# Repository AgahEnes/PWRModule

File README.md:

# PWRModule
In this article we introduce our power distribution modules. These boards help to get rid of long and heavy power cables. Circuit boards are reliable for connection instead of cables. Some of them distribute power to parallel or serial ways and others regulates high voltage power to desired values.
 PCB's have XT60 connector inputs for battery and XT60 outputs to power sensors or other kind of stuffs on our UAVs. Every output connection getting power from Li-Po battery and regulate this for desired value. By using resistors we adjust the out voltage. Both of the boards for our UAVs and for regulate power.
 One of them designed for unmanned ground vehicle (UGV) and is capable of meeting the power requirements of the onboard sensors and autopilot. There is also a motor drive system that will enable the UAG to move.
For orders https://jlcpcb.com/RAT is reliable.

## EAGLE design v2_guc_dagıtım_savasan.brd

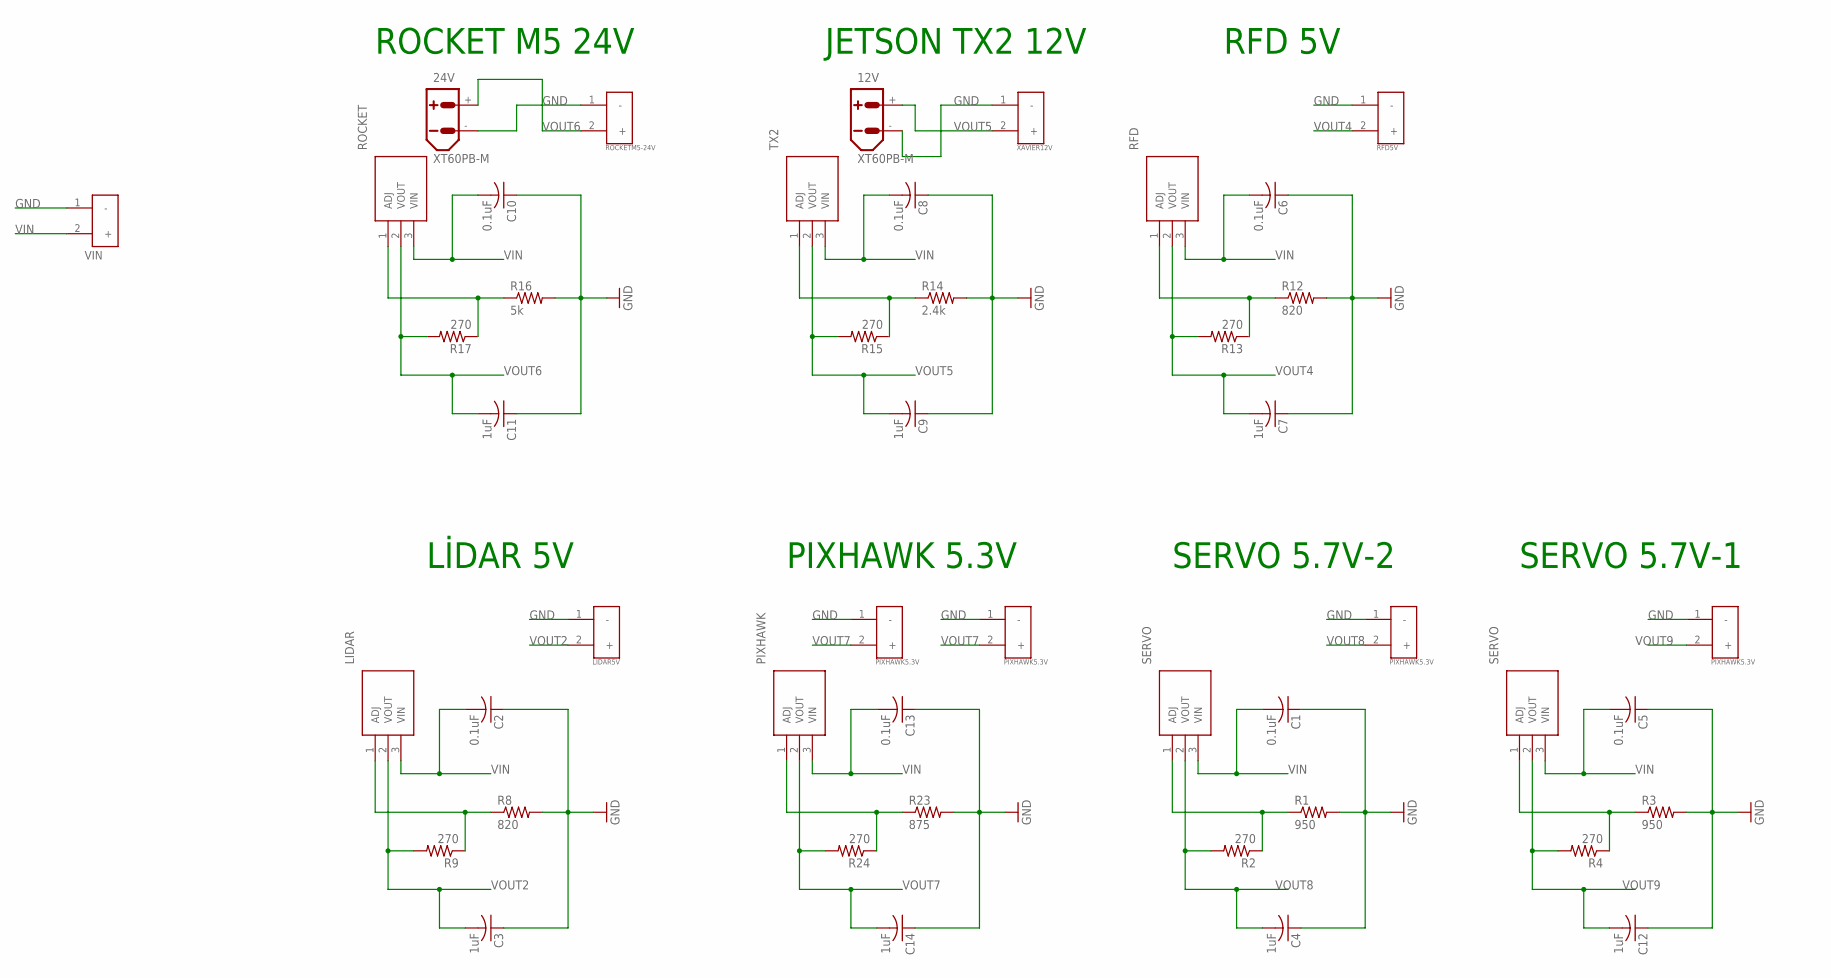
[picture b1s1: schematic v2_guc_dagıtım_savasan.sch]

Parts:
12V, 24V: XT60PB-M
C1, C2, C5, C6, C8, C10, C13: 0.1uF; C0402K
C3, C4, C7, C9, C11, C12, C14: 1uF; C0402K
IC5: LIDAR; TO254P470X1028X1955-3P
IC7: RFD; TO254P470X1028X1955-3P
IC8: TX2; TO254P470X1028X1955-3P
IC9: ROCKET; TO254P470X1028X1955-3P
IC13: PIXHAWK; TO254P470X1028X1955-3P
J3: VIN; AMASS_XT60-M
LIDAR5V: LIDAR5V; AMASS_XT60-M
PIXHAWK5.3V-1, PIXHAWK5.3V-2: PIXHAWK5.3V; AMASS_XT60-M
R1, R3: 950; R0805
R2, R4, R9, R13, R15, R17, R24: 270; R0805
R8, R12: 820; R0805
R14: 2.4k; R0805
R16: 5k; R0805
R23: 875; R0805
RFD5V: RFD5V; AMASS_XT60-M
ROCKETM5-24V: ROCKETM5-24V; AMASS_XT60-M
SERVO5.7V-1, SERVO5.7V-2: PIXHAWK5.3V; AMASS_XT60-M
SERVO-1, SERVO-2: SERVO; TO254P470X1028X1955-3P
TX2-12V: XAVIER12V; AMASS_XT60-M

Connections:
GND: 12V.-, 24V.-, C1.1, C2.1, C3.1, C4.1, C5.1, C6.1, C7.1, C8.1, C9.1, C10.1, C11.1, C12.1, C13.1, C14.1, J3.1 (-), LIDAR5V.1 (-), PIXHAWK5.3V-1.1 (-), PIXHAWK5.3V-2.1 (-), R1.2, R3.2, R8.2, R12.2, R14.2, R16.2, R23.2, RFD5V.1 (-), ROCKETM5-24V.1 (-), SERVO5.7V-1.1 (-), SERVO5.7V-2.1 (-), TX2-12V.1 (-)
unnamed: R1.1, R2.1, SERVO-2.1 (ADJ)
unnamed: R3.1, R4.1, SERVO-1.1 (ADJ)
unnamed: IC7.1 (ADJ), R12.1, R13.1
unnamed: IC5.1 (ADJ), R8.1, R9.1
unnamed: IC8.1 (ADJ), R14.1, R15.1
unnamed: IC9.1 (ADJ), R16.1, R17.1
unnamed: IC13.1 (ADJ), R23.1, R24.1
VIN: C1.2, C2.2, C5.2, C6.2, C8.2, C10.2, C13.2, IC5.3 (VIN), IC7.3 (VIN), IC8.3 (VIN), IC9.3 (VIN), IC13.3 (VIN), J3.2 (+), SERVO-1.3 (VIN), SERVO-2.3 (VIN)
VOUT2: C3.2, IC5.2 (VOUT), LIDAR5V.2 (+), R9.2
VOUT4: C7.2, IC7.2 (VOUT), R13.2, RFD5V.2 (+)
VOUT5: 12V.+, C9.2, IC8.2 (VOUT), R15.2, TX2-12V.2 (+)
VOUT6: 24V.+, C11.2, IC9.2 (VOUT), R17.2, ROCKETM5-24V.2 (+)
VOUT7: C14.2, IC13.2 (VOUT), PIXHAWK5.3V-1.2 (+), PIXHAWK5.3V-2.2 (+), R24.2
VOUT8: C4.2, R2.2, SERVO5.7V-2.2 (+), SERVO-2.2 (VOUT)
VOUT9: C12.2, R4.2, SERVO5.7V-1.2 (+), SERVO-1.2 (VOUT)

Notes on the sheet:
ROCKET M5 24V
JETSON TX2 12V
RFD 5V
LİDAR 5V
PIXHAWK 5.3V
SERVO 5.7V-2
SERVO 5.7V-1

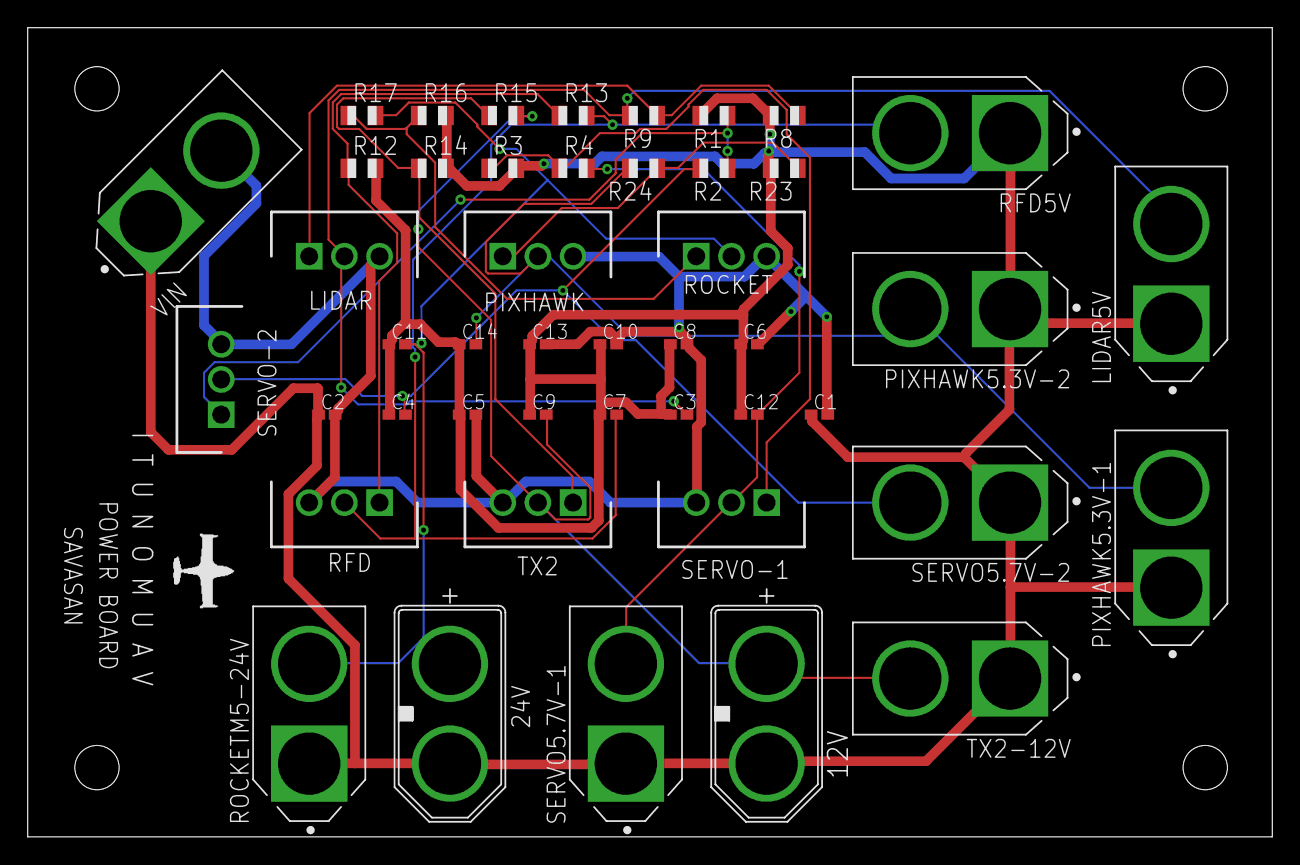
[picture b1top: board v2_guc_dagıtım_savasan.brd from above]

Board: 2 copper layers, 89.8 x 58.4 mm, 46 parts (0 on the bottom side), 16 nets.

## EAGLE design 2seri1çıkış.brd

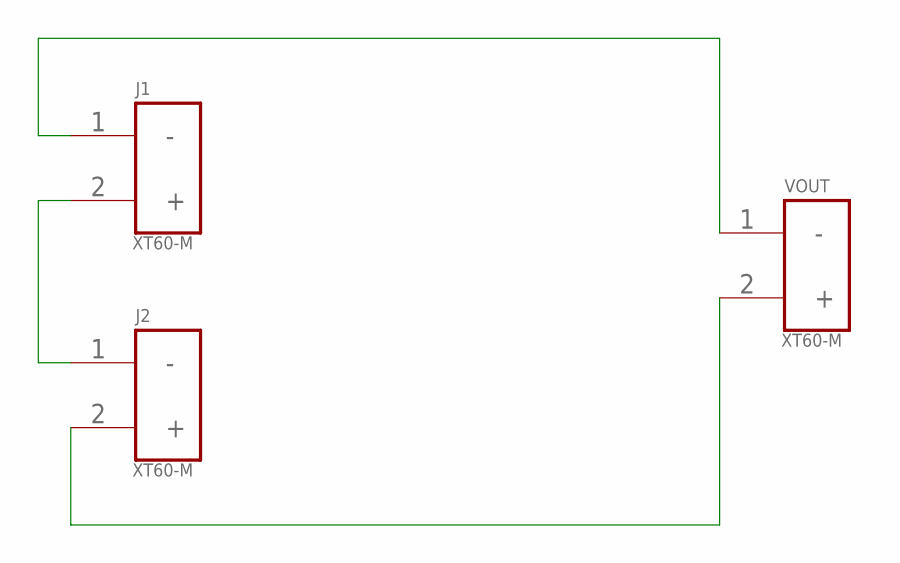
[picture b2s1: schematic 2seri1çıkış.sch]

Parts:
J1, J2: XT60-M; AMASS_XT60-M
VOUT: XT60-M; AMASS_XT60-M

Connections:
unnamed: J1.2 (+), J2.1 (-)
unnamed: J2.2 (+), VOUT.2 (+)
unnamed: J1.1 (-), VOUT.1 (-)

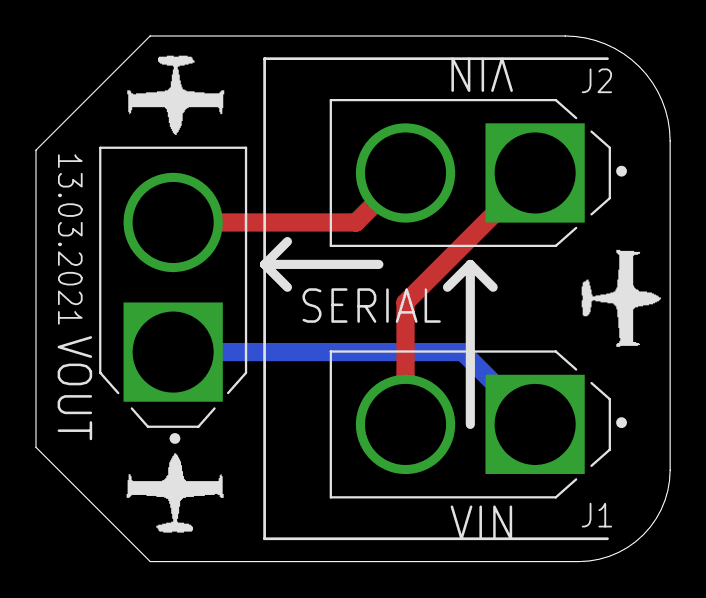
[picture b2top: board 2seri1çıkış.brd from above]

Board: 2 copper layers, 35.2 x 29.2 mm, 3 parts (0 on the bottom side), 3 nets.

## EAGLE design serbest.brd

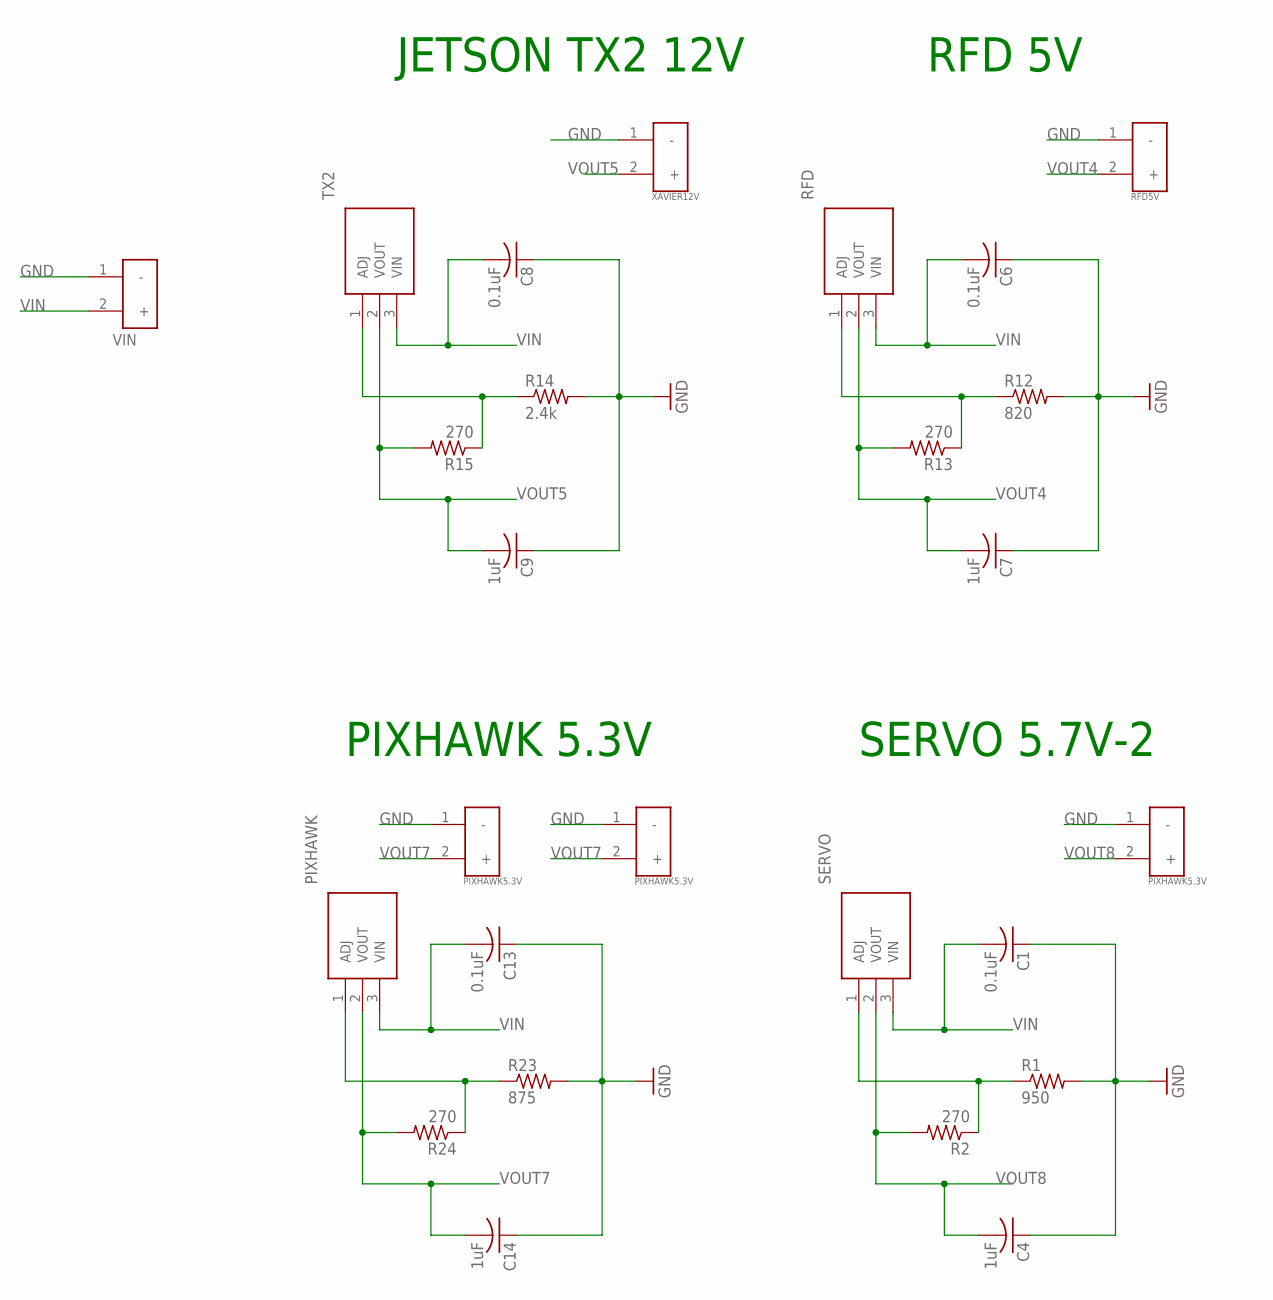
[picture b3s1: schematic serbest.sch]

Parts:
C1, C6, C8, C13: 0.1uF; C0402K
C4, C7, C9, C14: 1uF; C0402K
J3: VIN; AMASS_XT60-M
PIXHAWK: PIXHAWK; TO254P470X1028X1955-3P
PIXHAWK5.3V-1, PIXHAWK5.3V-2: PIXHAWK5.3V; AMASS_XT60-M
R1: 950; R0805
R2, R13, R15, R24: 270; R0805
R12: 820; R0805
R14: 2.4k; R0805
R23: 875; R0805
RFD: RFD; TO254P470X1028X1955-3P
RFD5V: RFD5V; AMASS_XT60-M
SERVO5.7V-2: PIXHAWK5.3V; AMASS_XT60-M
SERVO-2: SERVO; TO254P470X1028X1955-3P
TX2: TX2; TO254P470X1028X1955-3P
TX2-12V: XAVIER12V; AMASS_XT60-M

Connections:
GND: C1.1, C4.1, C6.1, C7.1, C8.1, C9.1, C13.1, C14.1, J3.1 (-), PIXHAWK5.3V-1.1 (-), PIXHAWK5.3V-2.1 (-), R1.2, R12.2, R14.2, R23.2, RFD5V.1 (-), SERVO5.7V-2.1 (-), TX2-12V.1 (-)
unnamed: R1.1, R2.1, SERVO-2.1 (ADJ)
unnamed: R12.1, R13.1, RFD.1 (ADJ)
unnamed: R14.1, R15.1, TX2.1 (ADJ)
unnamed: PIXHAWK.1 (ADJ), R23.1, R24.1
VIN: C1.2, C6.2, C8.2, C13.2, J3.2 (+), PIXHAWK.3 (VIN), RFD.3 (VIN), SERVO-2.3 (VIN), TX2.3 (VIN)
VOUT4: C7.2, R13.2, RFD.2 (VOUT), RFD5V.2 (+)
VOUT5: C9.2, R15.2, TX2.2 (VOUT), TX2-12V.2 (+)
VOUT7: C14.2, PIXHAWK.2 (VOUT), PIXHAWK5.3V-1.2 (+), PIXHAWK5.3V-2.2 (+), R24.2
VOUT8: C4.2, R2.2, SERVO5.7V-2.2 (+), SERVO-2.2 (VOUT)

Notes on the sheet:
JETSON TX2 12V
RFD 5V
PIXHAWK 5.3V
SERVO 5.7V-2

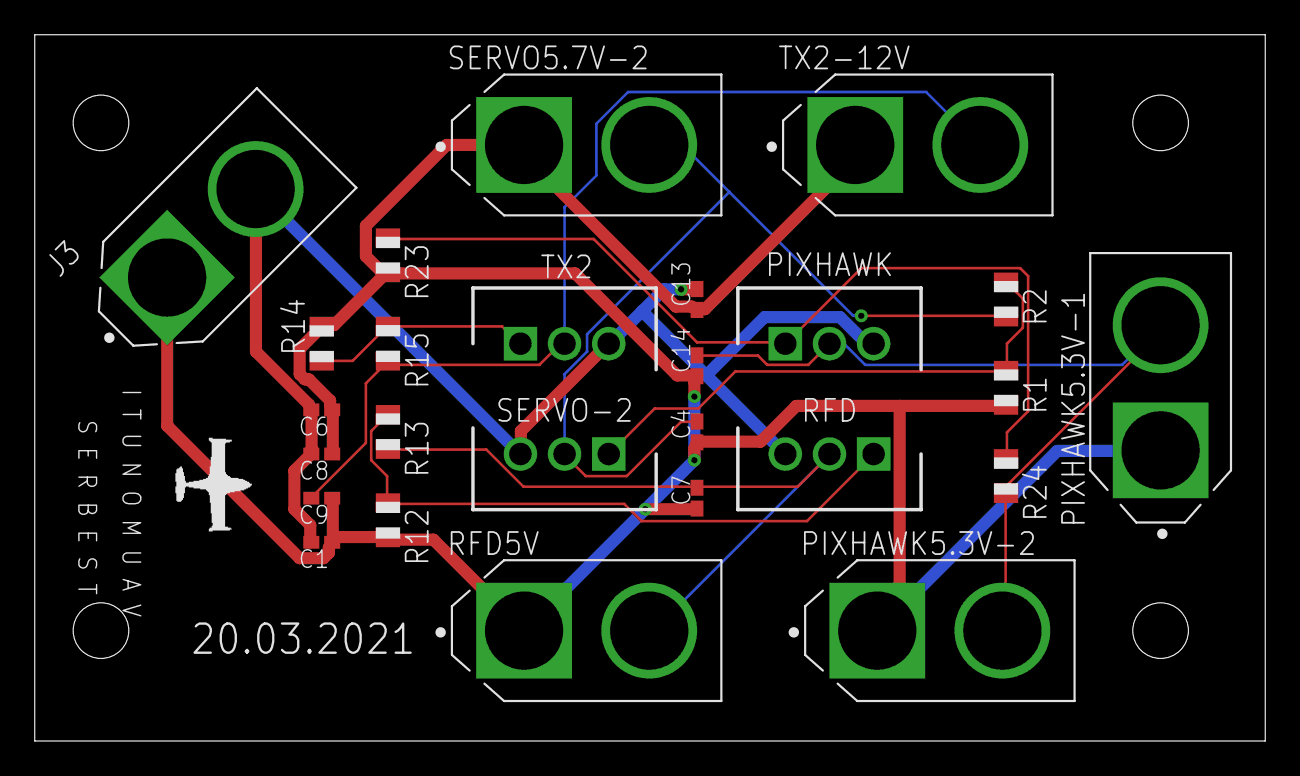
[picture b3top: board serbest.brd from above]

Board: 2 copper layers, 70.8 x 40.6 mm, 26 parts (0 on the bottom side), 10 nets.

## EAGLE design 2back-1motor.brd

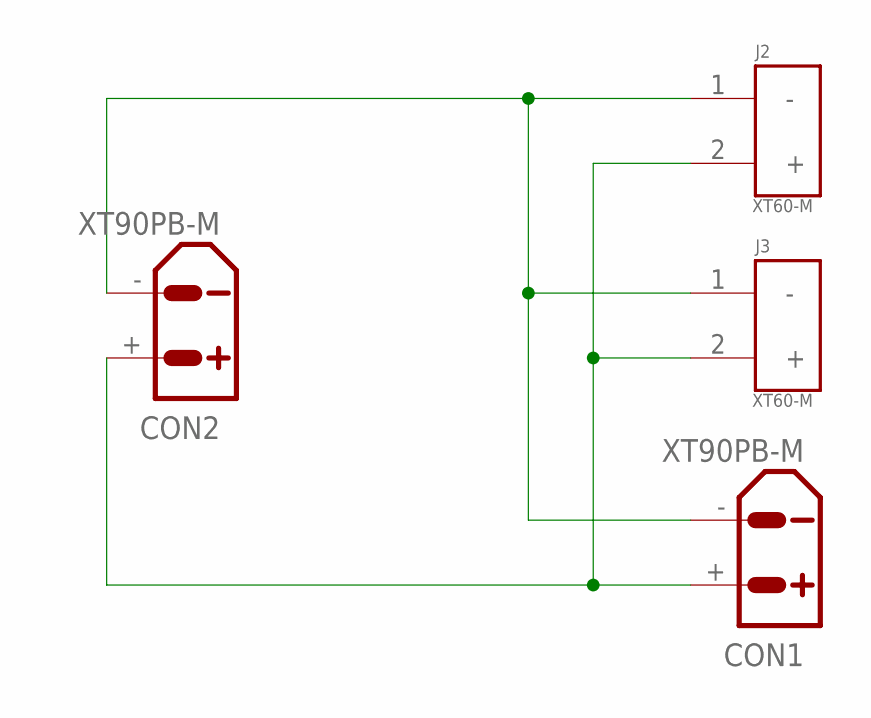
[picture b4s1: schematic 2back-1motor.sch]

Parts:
CON1, CON2: XT90PB-M
J2, J3: XT60-M; AMASS_XT60-M

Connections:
unnamed: CON1.-, CON2.-, J2.1 (-), J3.1 (-)
unnamed: CON1.+, CON2.+, J2.2 (+), J3.2 (+)

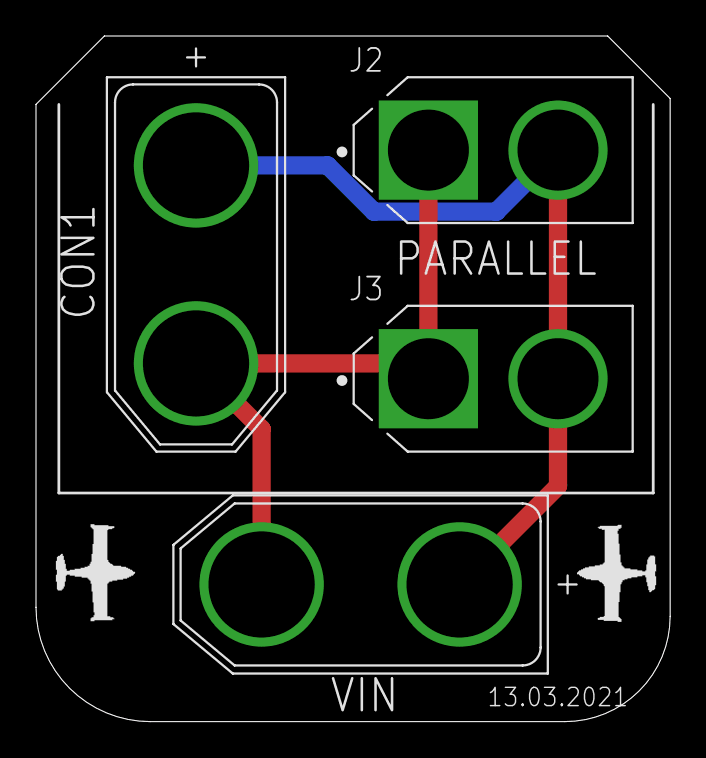
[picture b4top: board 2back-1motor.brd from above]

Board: 2 copper layers, 35.2 x 38.1 mm, 4 parts (0 on the bottom side), 2 nets.

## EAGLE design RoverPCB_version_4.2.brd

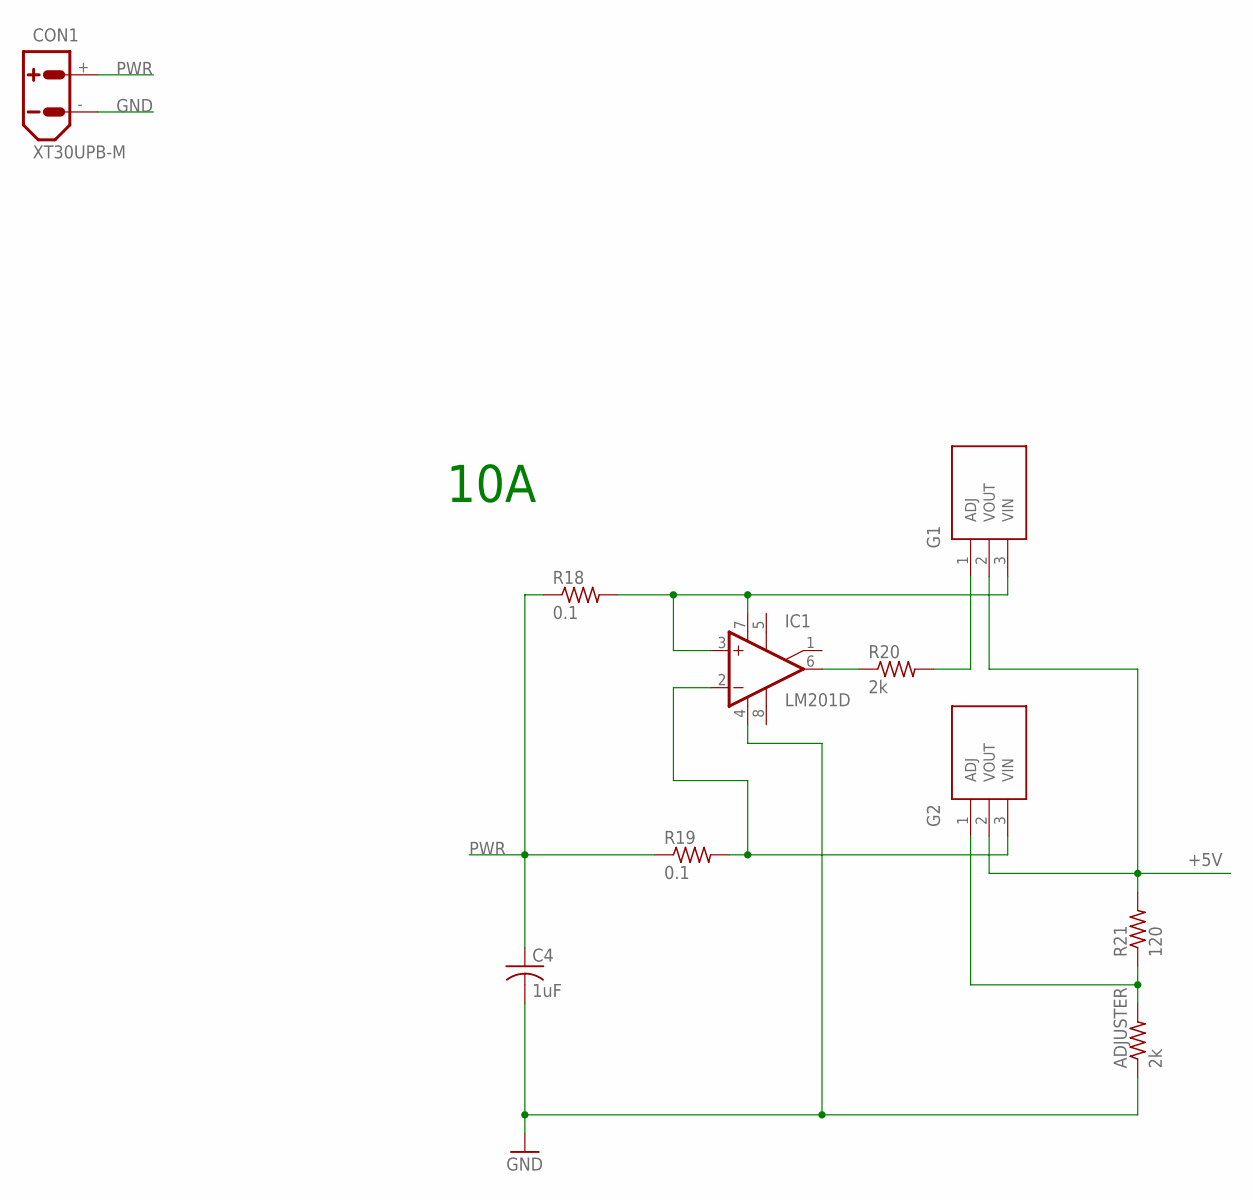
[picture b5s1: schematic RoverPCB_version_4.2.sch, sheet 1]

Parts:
ADJUSTER: 2k; 0204/5
C4: 1uF; C0402K
CON1: XT30UPB-M
IC1: LM201D; SO08
IC11: G1; TO254P470X1028X1955-3P
IC12: G2; TO254P470X1028X1955-3P
R18, R19: 0.1; M1206
R20: 2k; R0805
R21: 120; R0805

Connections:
+5V: IC11.2 (VOUT), IC12.2 (VOUT), R21.2; also elsewhere on the board
GND: ADJUSTER.1, C4.2, CON1.-, IC1.4 (V-); also elsewhere on the board
unnamed: IC11.1 (ADJ), R20.2
unnamed: IC1.6 (OUT), R20.1
unnamed: ADJUSTER.2, IC12.1 (ADJ), R21.1
unnamed: IC1.3 (+IN), IC1.7 (V+), IC11.3 (VIN), R18.2
unnamed: IC1.2 (-IN), IC12.3 (VIN), R19.2
PWR: C4.1, CON1.+, R18.1, R19.1; also elsewhere on the board

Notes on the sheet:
10A

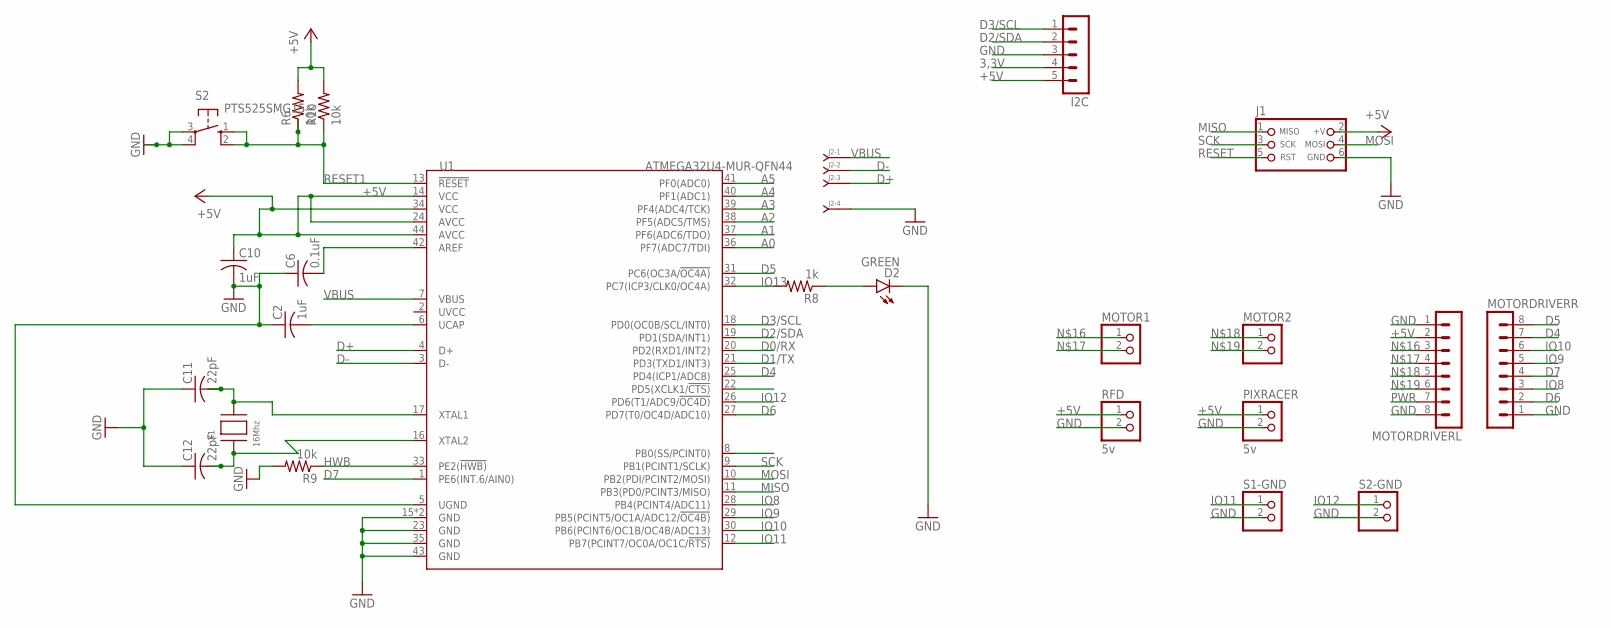
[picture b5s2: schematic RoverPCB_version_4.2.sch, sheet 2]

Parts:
C2, C10: 1uF; C0805
C6: 0.1uF; C0805
C11, C12: 22pF; C0805
D2: GREEN; LED-0603
I2C: MA05-1
J1: CON_HEADER_PRG_AVR_ICSP-PTH; HEADER_PRG_2X03
J2: J-04-SIP-100; SIP-100-04
MOTOR1, MOTOR2: PINHD-1X2; 1X02
MOTORDRIVERL: MA08-1
MOTORDRIVERR: MA08-1
PIXRACER: 5v; 1X02
R6, R9, R10: 10k; R0805
R8: 1k; R0805
RFD: 5v; 1X02
S1-GND, S2-GND: PINHD-1X2; 1X02
S2: PTS525SMG15; SMG15
U1: ATMEGA32U4-MUR-QFN44; QFN44G-0.5-7X7MM
X1: 16Mhz; NX5032

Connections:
3,3V: I2C.4
+5V: C10.1, I2C.5, J1.2 (+V), MOTORDRIVERL.2, PIXRACER.1, R6.2, R10.2, RFD.1, U1.14 (VCC), U1.24 (AVCC), U1.34 (VCC), U1.44 (AVCC); also elsewhere on the board
A0: U1.36 (PF7(ADC7/TDI))
A1: U1.37 (PF6(ADC6/TDO))
A2: U1.38 (PF5(ADC5/TMS))
A3: U1.39 (PF4(ADC4/TCK))
A4: U1.40 (PF1(ADC1))
A5: U1.41 (PF0(ADC0))
D0/RX: U1.20 (PD2(RXD1/INT2))
D1/TX: U1.21 (PD3(TXD1/INT3))
D2/SDA: I2C.2, U1.19 (PD1(SDA/INT1))
D3/SCL: I2C.1, U1.18 (PD0(OC0B/SCL/INT0))
D4: MOTORDRIVERR.7, U1.25 (PD4(ICP1/ADC8))
D5: MOTORDRIVERR.8, U1.31 (PC6(OC3A/!OC4A))
D6: MOTORDRIVERR.2, U1.27 (PD7(T0/OC4D/ADC10))
D7: MOTORDRIVERR.4, U1.1 (PE6(INT.6/AIN0))
D+: J2.3, U1.4 (D+)
D-: J2.2, U1.3 (D-)
GND: C2.1, C6.1, C10.2, C11.1, C12.1, D2.C, I2C.3, J1.6 (GND), J2.4, MOTORDRIVERL.1, MOTORDRIVERL.8, MOTORDRIVERR.1, PIXRACER.2, R9.2, RFD.2, S1-GND.2, S2.3, S2.4, S2-GND.2, U1.5 (UGND), U1.15 (GND), U1.23 (GND), U1.35 (GND), U1.43 (GND), U1.TAB (GND); also elsewhere on the board
HWB: R9.1, U1.33 (PE2(!HWB))
IO8: MOTORDRIVERR.3, U1.28 (PB4(PCINT4/ADC11))
IO9: MOTORDRIVERR.5, U1.29 (PB5(PCINT5/OC1A/ADC12/!OC4B))
IO10: MOTORDRIVERR.6, U1.30 (PB6(PCINT6/OC1B/OC4B/ADC13))
IO11: S1-GND.1, U1.12 (PB7(PCINT7/OC0A/OC1C/!RTS))
IO12: S2-GND.1, U1.26 (PD6(T1/ADC9/!OC4D))
IO13: R8.2, U1.32 (PC7(ICP3/CLK0/OC4A))
MISO: J1.1 (MISO), U1.11 (PB3(PD0/PCINT3/MISO))
MOSI: J1.4 (MOSI), U1.10 (PB2(PDI/PCINT2/MOSI))
unnamed: D2.A, R8.1
unnamed: C11.2, U1.17 (XTAL1), X1.P$2
unnamed: C2.2, U1.6 (UCAP)
unnamed: C12.2, U1.16 (XTAL2), X1.P$1
unnamed: C6.2, U1.42 (AREF)
unnamed: MOTOR1.1, MOTORDRIVERL.3
unnamed: MOTOR1.2, MOTORDRIVERL.4
unnamed: MOTOR2.1, MOTORDRIVERL.5
unnamed: MOTOR2.2, MOTORDRIVERL.6
PWR: MOTORDRIVERL.7; also elsewhere on the board
RESET: J1.5 (RST)
RESET1: R6.1, R10.1, S2.1 (S), S2.2 (S), U1.13 (!RESET)
SCK: J1.3 (SCK), U1.9 (PB1(PCINT1/SCLK))
VBUS: J2.1, U1.7 (VBUS)

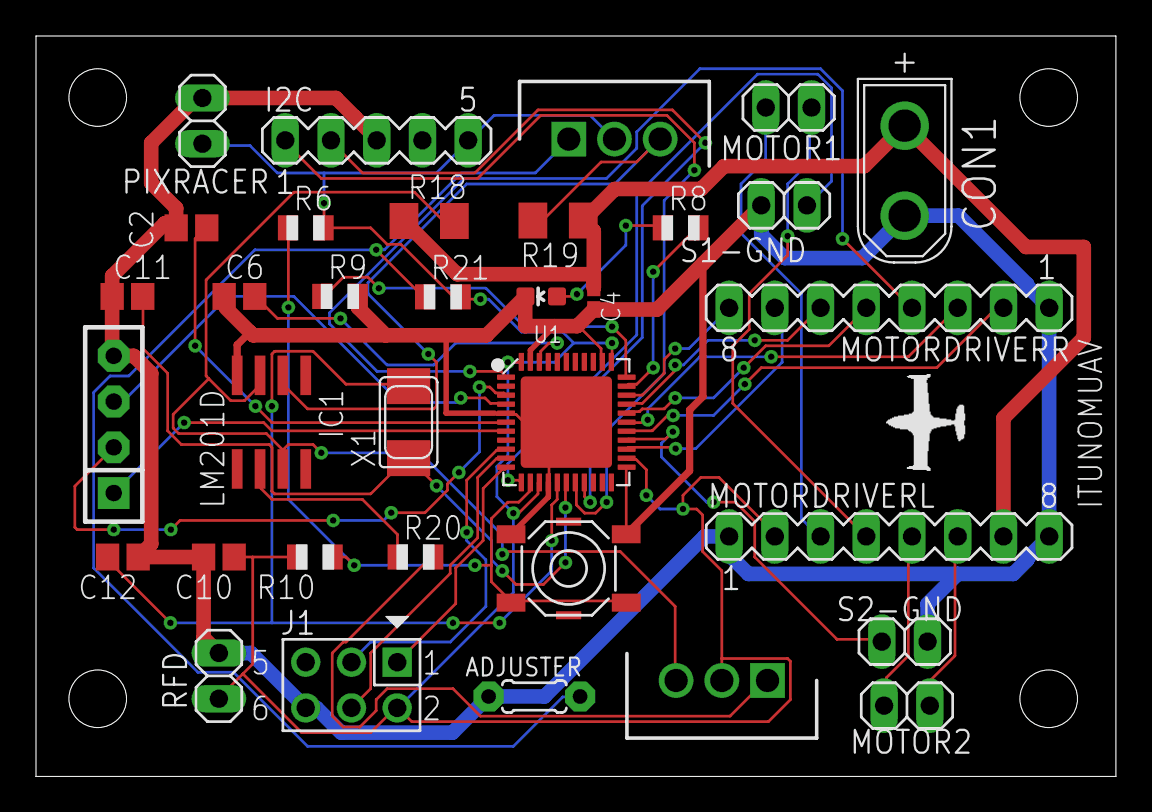
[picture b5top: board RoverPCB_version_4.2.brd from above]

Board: 2 copper layers, 60.0 x 41.1 mm, 34 parts (0 on the bottom side), 37 nets.

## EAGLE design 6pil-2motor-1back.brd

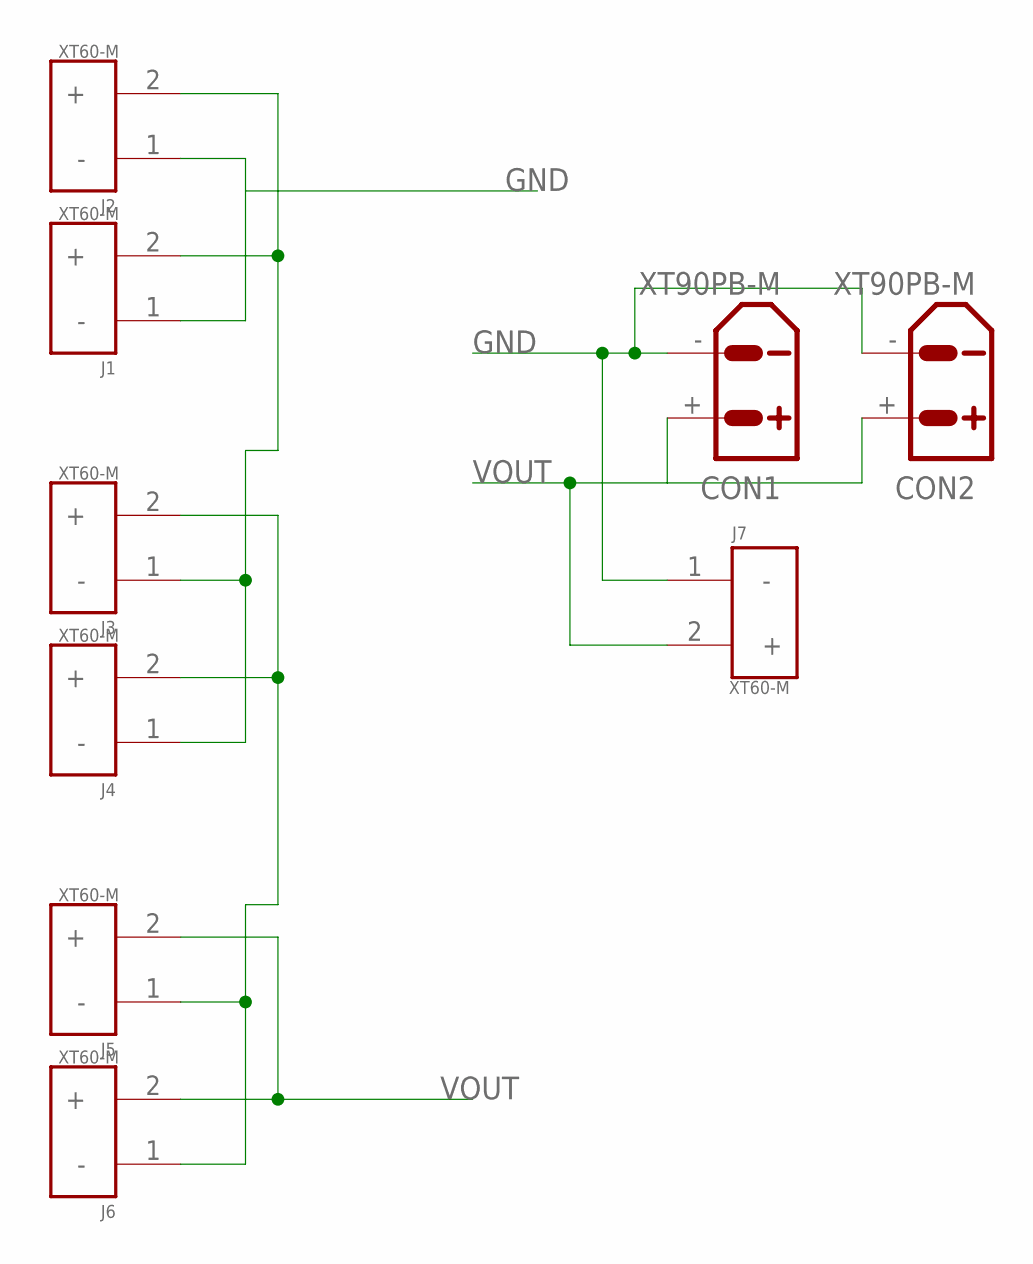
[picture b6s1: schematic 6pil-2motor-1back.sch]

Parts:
CON1, CON2: XT90PB-M
J1, J2, J3, J4, J5, J6, J7: XT60-M; AMASS_XT60-M

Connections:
GND: CON1.-, CON2.-, J1.1 (-), J2.1 (-), J7.1 (-)
unnamed: J1.2 (+), J2.2 (+), J3.1 (-), J4.1 (-)
unnamed: J3.2 (+), J4.2 (+), J5.1 (-), J6.1 (-)
VOUT: CON1.+, CON2.+, J5.2 (+), J6.2 (+), J7.2 (+)

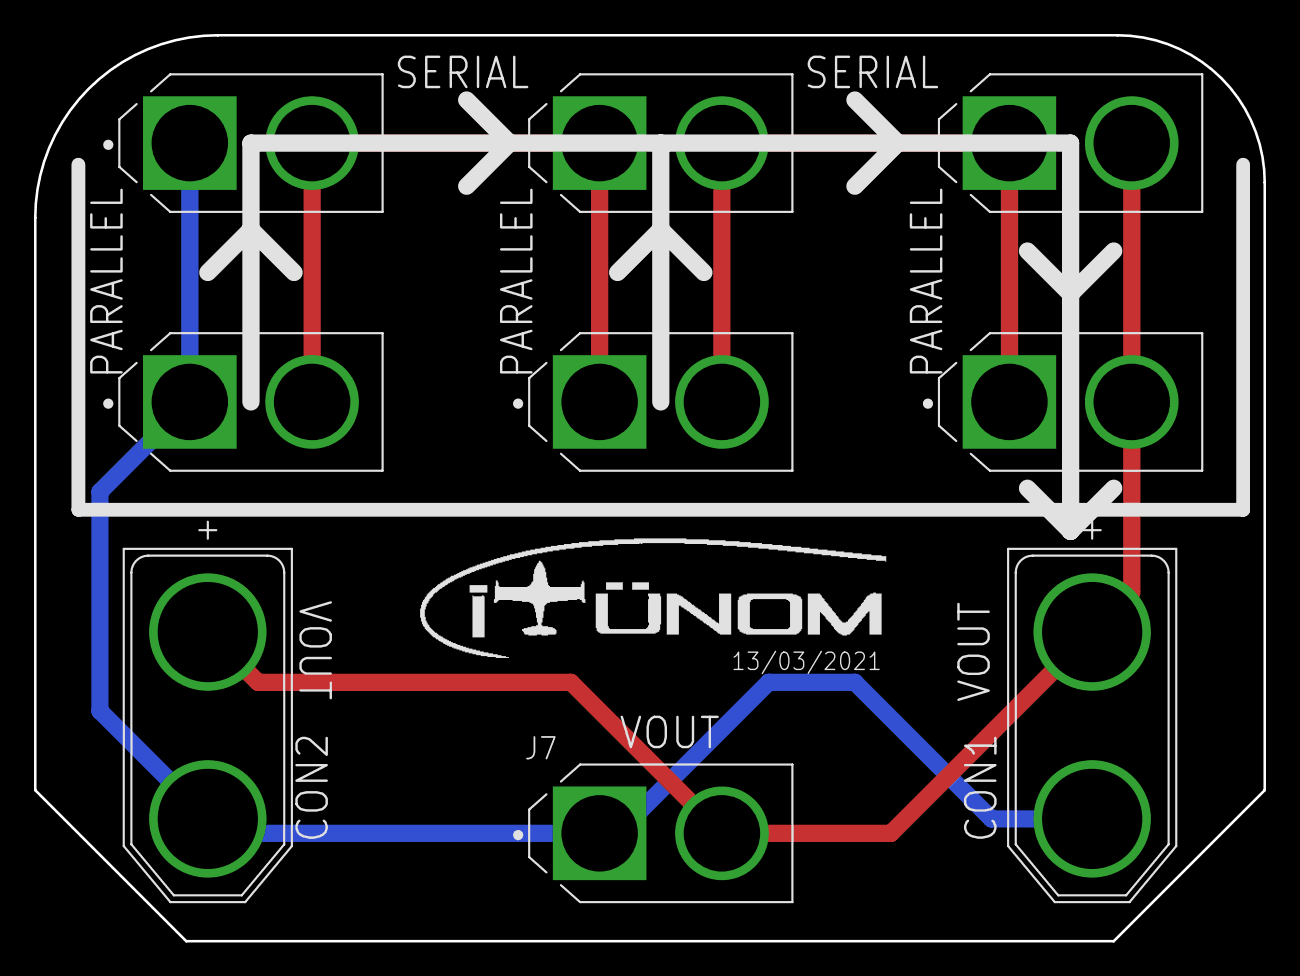
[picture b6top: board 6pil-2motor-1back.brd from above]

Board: 2 copper layers, 72.4 x 53.3 mm, 9 parts (0 on the bottom side), 4 nets.

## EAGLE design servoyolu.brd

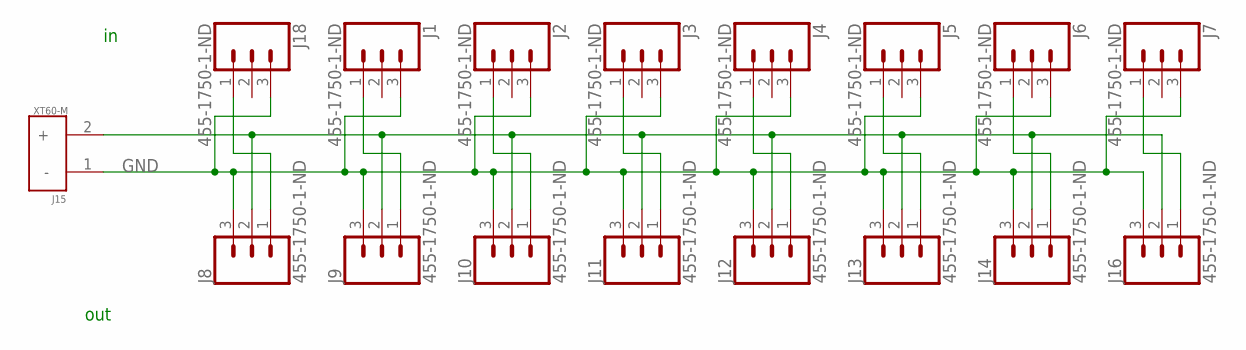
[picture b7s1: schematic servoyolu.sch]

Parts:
J1, J2, J3, J4, J5, J6, J7, J8, J9, J10, J11, J12, J13, J14, J16, J18: 455-1750-1-ND; 1X03
J15: XT60-M; AMASS_XT60-M

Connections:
GND: J1.3, J2.3, J3.3, J4.3, J5.3, J6.3, J7.3, J8.3, J9.3, J10.3, J11.3, J12.3, J13.3, J14.3, J15.1 (-), J16.3, J18.3
unnamed: J8.1, J18.1
unnamed: J1.1, J9.1
unnamed: J2.1, J10.1
unnamed: J3.1, J11.1
unnamed: J4.1, J12.1
unnamed: J5.1, J13.1
unnamed: J6.1, J14.1
unnamed: J7.1, J16.1
unnamed: J8.2, J9.2, J10.2, J11.2, J12.2, J13.2, J14.2, J15.2 (+), J16.2

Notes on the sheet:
out

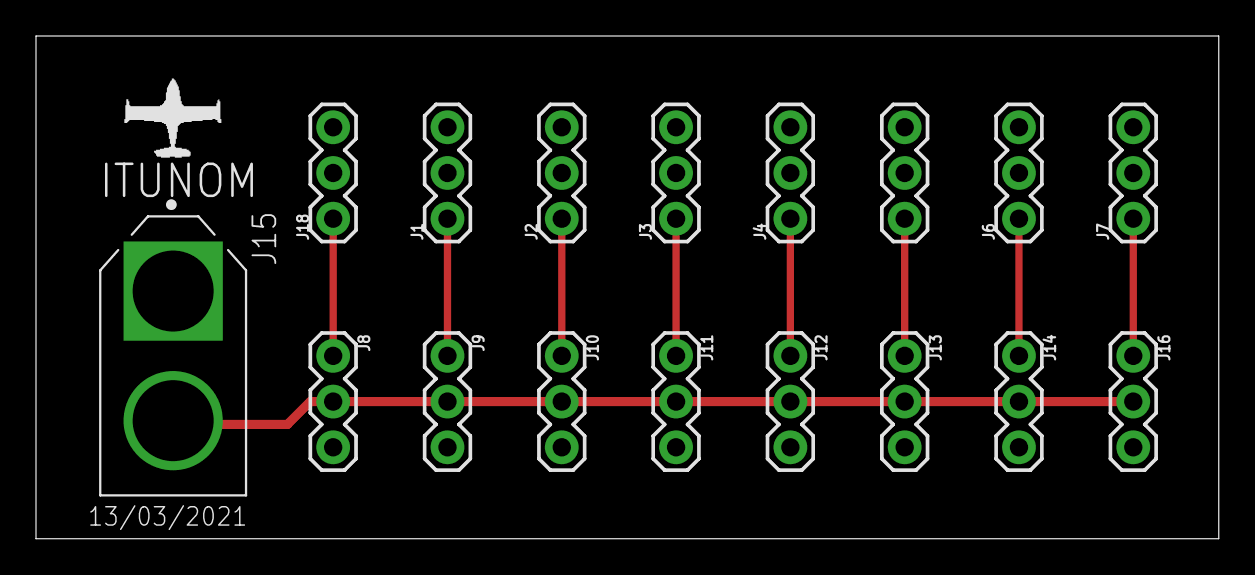
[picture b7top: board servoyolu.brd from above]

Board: 2 copper layers, 65.7 x 27.9 mm, 17 parts (0 on the bottom side), 10 nets.

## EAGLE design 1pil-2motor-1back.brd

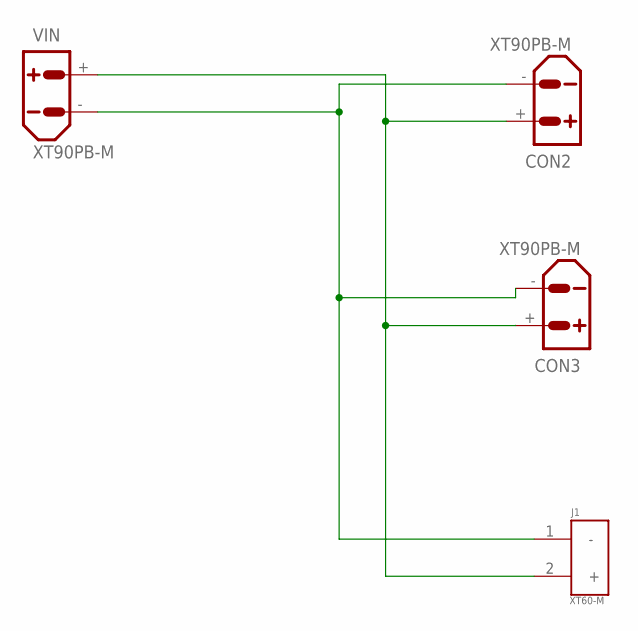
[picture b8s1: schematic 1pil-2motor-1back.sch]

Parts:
CON2, CON3: XT90PB-M
J1: XT60-M; AMASS_XT60-M
VIN: XT90PB-M

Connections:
unnamed: CON2.+, CON3.+, J1.2 (+), VIN.+
unnamed: CON2.-, CON3.-, J1.1 (-), VIN.-

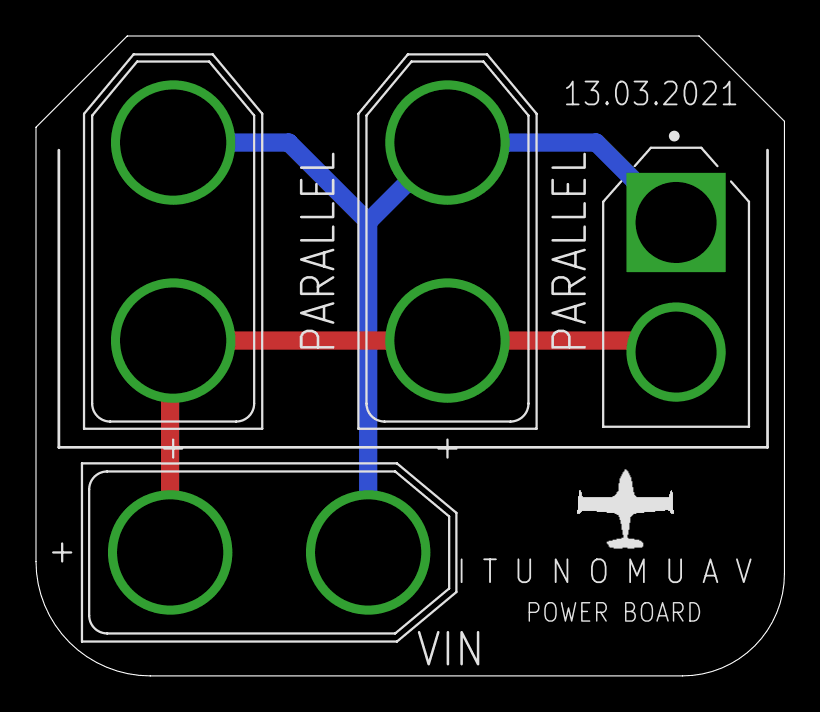
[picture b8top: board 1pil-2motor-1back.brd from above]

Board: 2 copper layers, 41.6 x 35.5 mm, 4 parts (0 on the bottom side), 2 nets.

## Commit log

2021-04-05 https://jlcpcb.com/RAT
    https://jlcpcb.com/RAT

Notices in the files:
parts and their libraries:
SparkFun-LED: Licensing: Creative Commons ShareAlike 4.0 International - https://creativecommons.org/licenses/by-sa/4.0
con-headers-jp: Copyright (C) 2004, Bob Starr (rtzaudio@mindspring.com)
